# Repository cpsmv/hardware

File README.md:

# CPSMV EAGLE Library Specifications #

Please follow these guidelines for all PCBs for the Supermileage vehicle.

### EAGLE: 

##### Schematic:
   * Grid size: 100 mil (default)

##### PCB Layout:
   * Silkscreen text size:   40 mil 
   * Silkscreen text ratio:  15% 
   * Silkscreen text font:   Vector 

##### Gerbers:

When generating Gerbers, please use the following layers:
   * 1  - Top 
   * 16 - Bottom
   * 17 - Pads
   * 18 - Vias
   * 21 - tPlace
   * 22 - bPlace (if any silkscreen on bottom of board)
   * 25 - tNames
   * 27 - tValues
   * 29 - tStop
   * 39 - tKeepout
   * 44 - Drills
   * 45 - Holes

Notes:
   * Use layers 2-15 if the board is more than 2 layers 
   * Layer 51 tDocu & 52 bDocu are not to be used for silkscreen

### Advanced Circuits: 
   * General fab specs:    http://www.4pcb.com/pcb-design-specifications/ 
   * 2 layer board specs:  http://www.4pcb.com/33-each-pcbs/index.html 
   * 4 layer board specs:  http://www.4pcb.com/66-each-pcbs/index.html

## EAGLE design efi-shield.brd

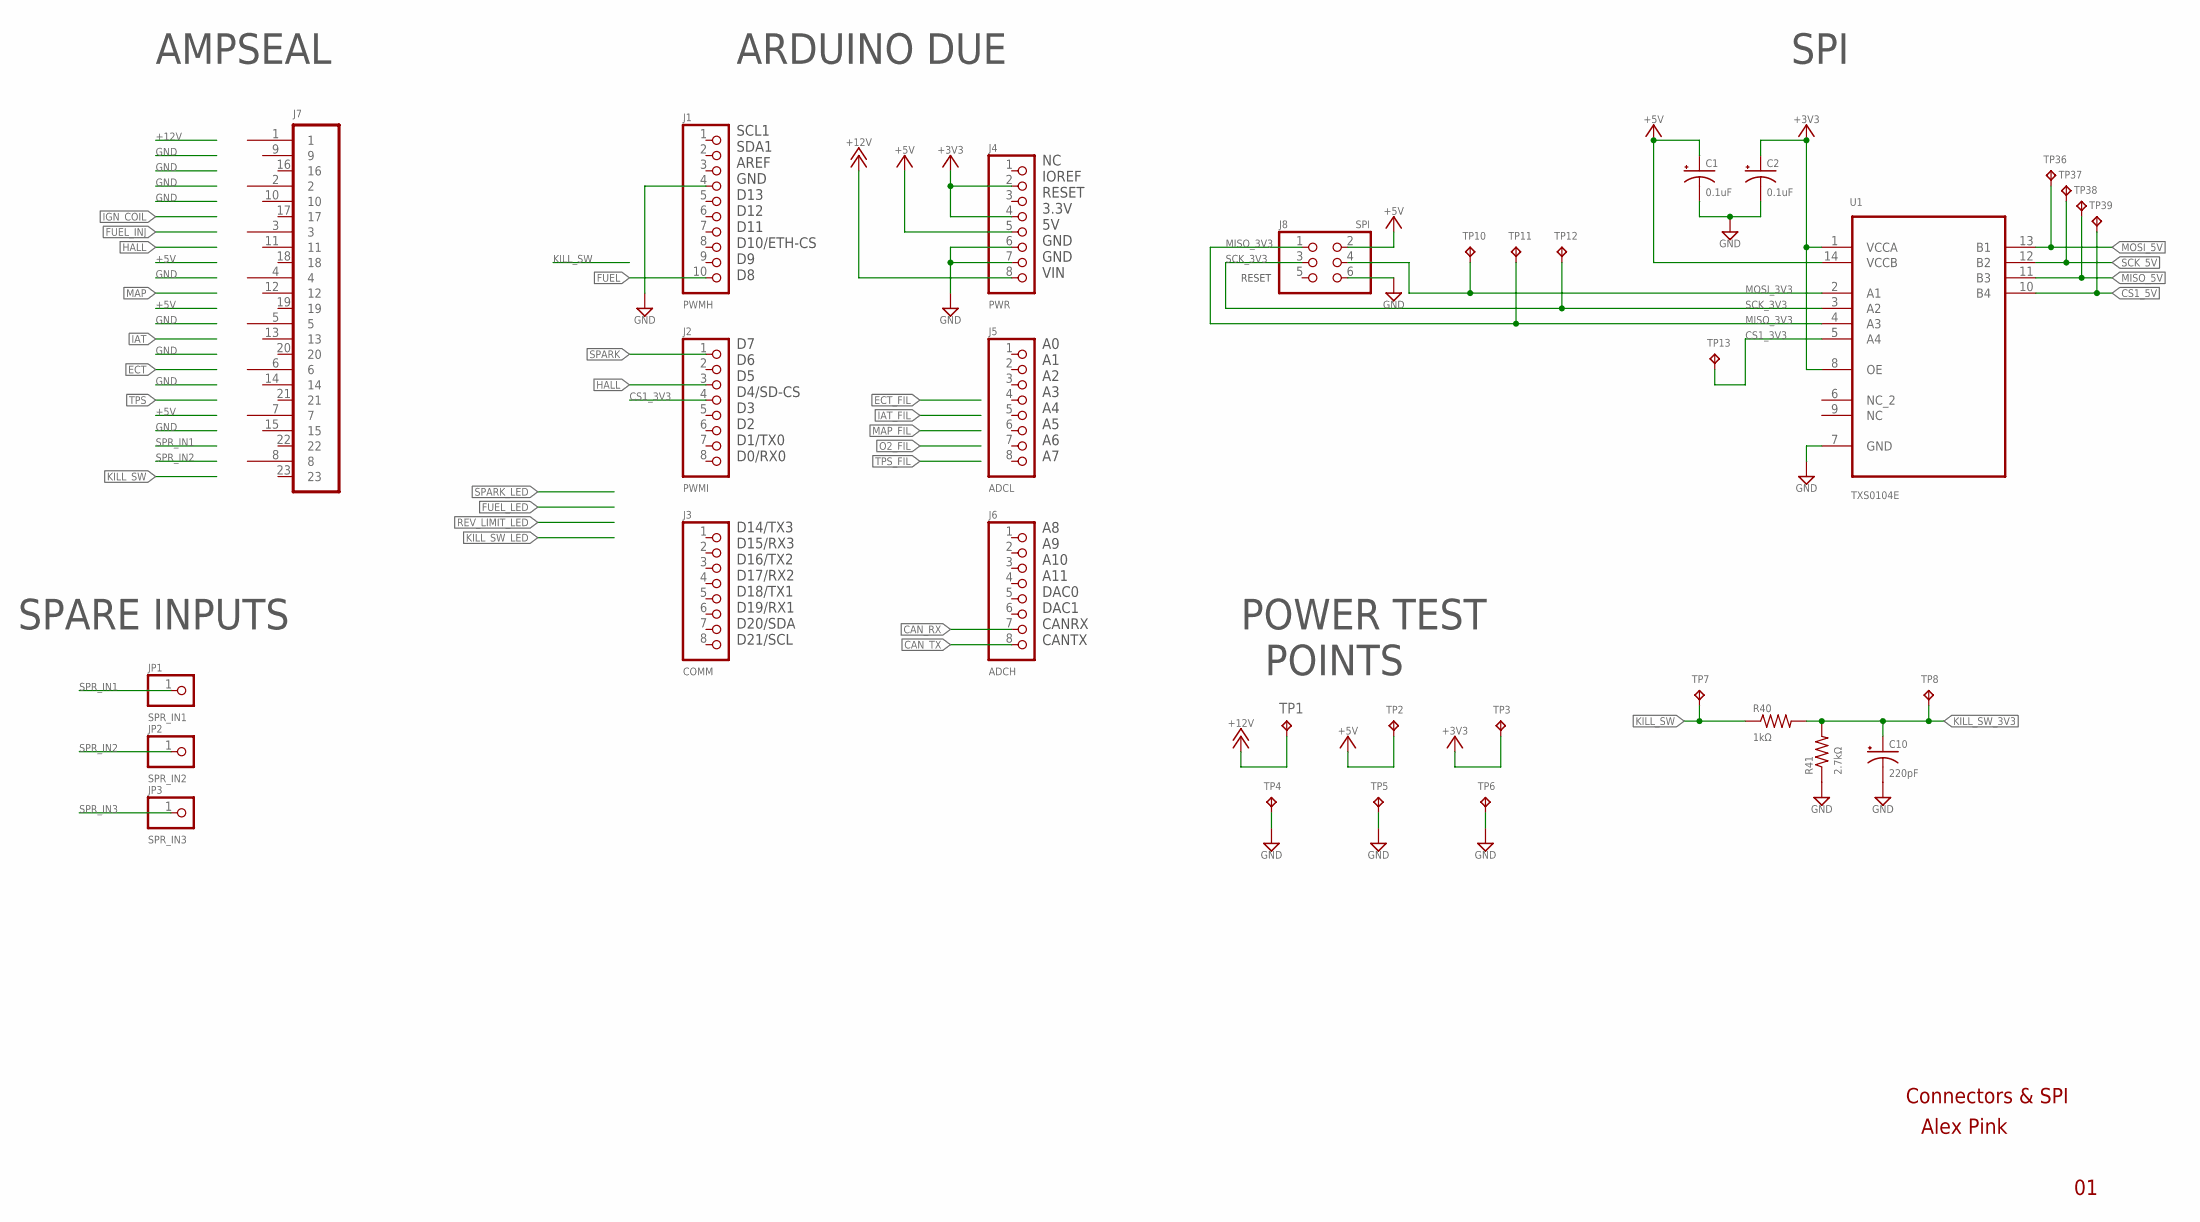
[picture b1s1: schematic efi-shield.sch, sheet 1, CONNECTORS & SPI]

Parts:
C1, C2: 0.1uF; C050-025X075
C10: 220pF; C050-025X075
J1: PWMH; 1X10
J2: PWMI; 1X08
J3: COMM; 1X08
J4: PWR; 1X08
J5: ADCL; 1X08
J6: ADCH; 1X08
J7: AMPSEAL-23POS-HEADER; AMPSEAL-HEADER-23POS-RA
J8: SPI; 2X03
JP1: SPR_IN1; 1X01
JP2: SPR_IN2; 1X01
JP3: SPR_IN3; 1X01
R40: 1kΩ; 0207/7
R41: 2.7kΩ; 0207/7
TP1: +12V; TP-P1-20
TP2: +5V; TP-P1-20
TP3: +3V3; TP-P1-20
TP4, TP5, TP6: GND; TP-P1-20
TP7: KILL_SW; TP-P1-20
TP8: KILL_SW_3V3; TP-P1-20
TP10: MOSI_3V3; TP-P1-20
TP11: MISO_3V3; TP-P1-20
TP12: SCK_3V3; TP-P1-20
TP13: CS1_3V3; TP-P1-20
TP36: MOSI_5V; TP-P1-20
TP37: SCK_5V; TP-P1-20
TP38: MISO_5V; TP-P1-20
TP39: CS1_5V; TP-P1-20
U1: TXS0104E; SOIC127P600X175-14N

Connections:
+3V3: C2.1, J4.2, J4.4, TP3.TP, U1.1 (VCCA), U1.8 (OE)
+5V: C1.1, J4.5, J8.2, TP2.TP, U1.14 (VCCB); also elsewhere on the board
+12V: J4.8, TP1.TP; also elsewhere on the board
CAN_RX: J6.7; also elsewhere on the board
CAN_TX: J6.8; also elsewhere on the board
CS1_3V3: J2.4, TP13.TP, U1.5 (A4)
CS1_5V: TP39.TP, U1.10 (B4)
FUEL: J1.10; also elsewhere on the board
GND: C1.2, C2.2, C10.2, J1.4, J4.6, J4.7, J8.6, R41.1, TP4.TP, TP5.TP, TP6.TP, U1.7 (GND); also elsewhere on the board
HALL: J2.3; also elsewhere on the board
KILL_SW: R40.1, TP7.TP
KILL_SW_3V3: C10.1, R40.2, R41.2, TP8.TP
MISO_3V3: J8.1, TP11.TP, U1.4 (A3)
MISO_5V: TP38.TP, U1.11 (B3)
MOSI_3V3: J8.4, TP10.TP, U1.2 (A1)
MOSI_5V: TP36.TP, U1.13 (B1)
SCK_3V3: J8.3, TP12.TP, U1.3 (A2)
SCK_5V: TP37.TP, U1.12 (B2)
SPARK: J2.1; also elsewhere on the board
SPR_IN1: JP1.1
SPR_IN2: JP2.1
SPR_IN3: JP3.1

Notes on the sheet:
SCL1 SDA1 AREF GND D13 D12 D11 D10/ETH-CS D9 D8
D7 D6 D5 D4/SD-CS D3 D2 D1/TX0 D0/RX0
D14/TX3 D15/RX3 D16/TX2 D17/RX2 D18/TX1 D19/RX1 D20/SDA D21/SCL
NC IOREF RESET 3.3V 5V GND GND VIN
A0 A1 A2 A3 A4 A5 A6 A7
A8 A9 A10 A11 DAC0 DAC1 CANRX CANTX
ARDUINO DUE
AMPSEAL
RESET
SPI
SPARE INPUTS
Alex Pink
Connectors & SPI
POWER TEST POINTS

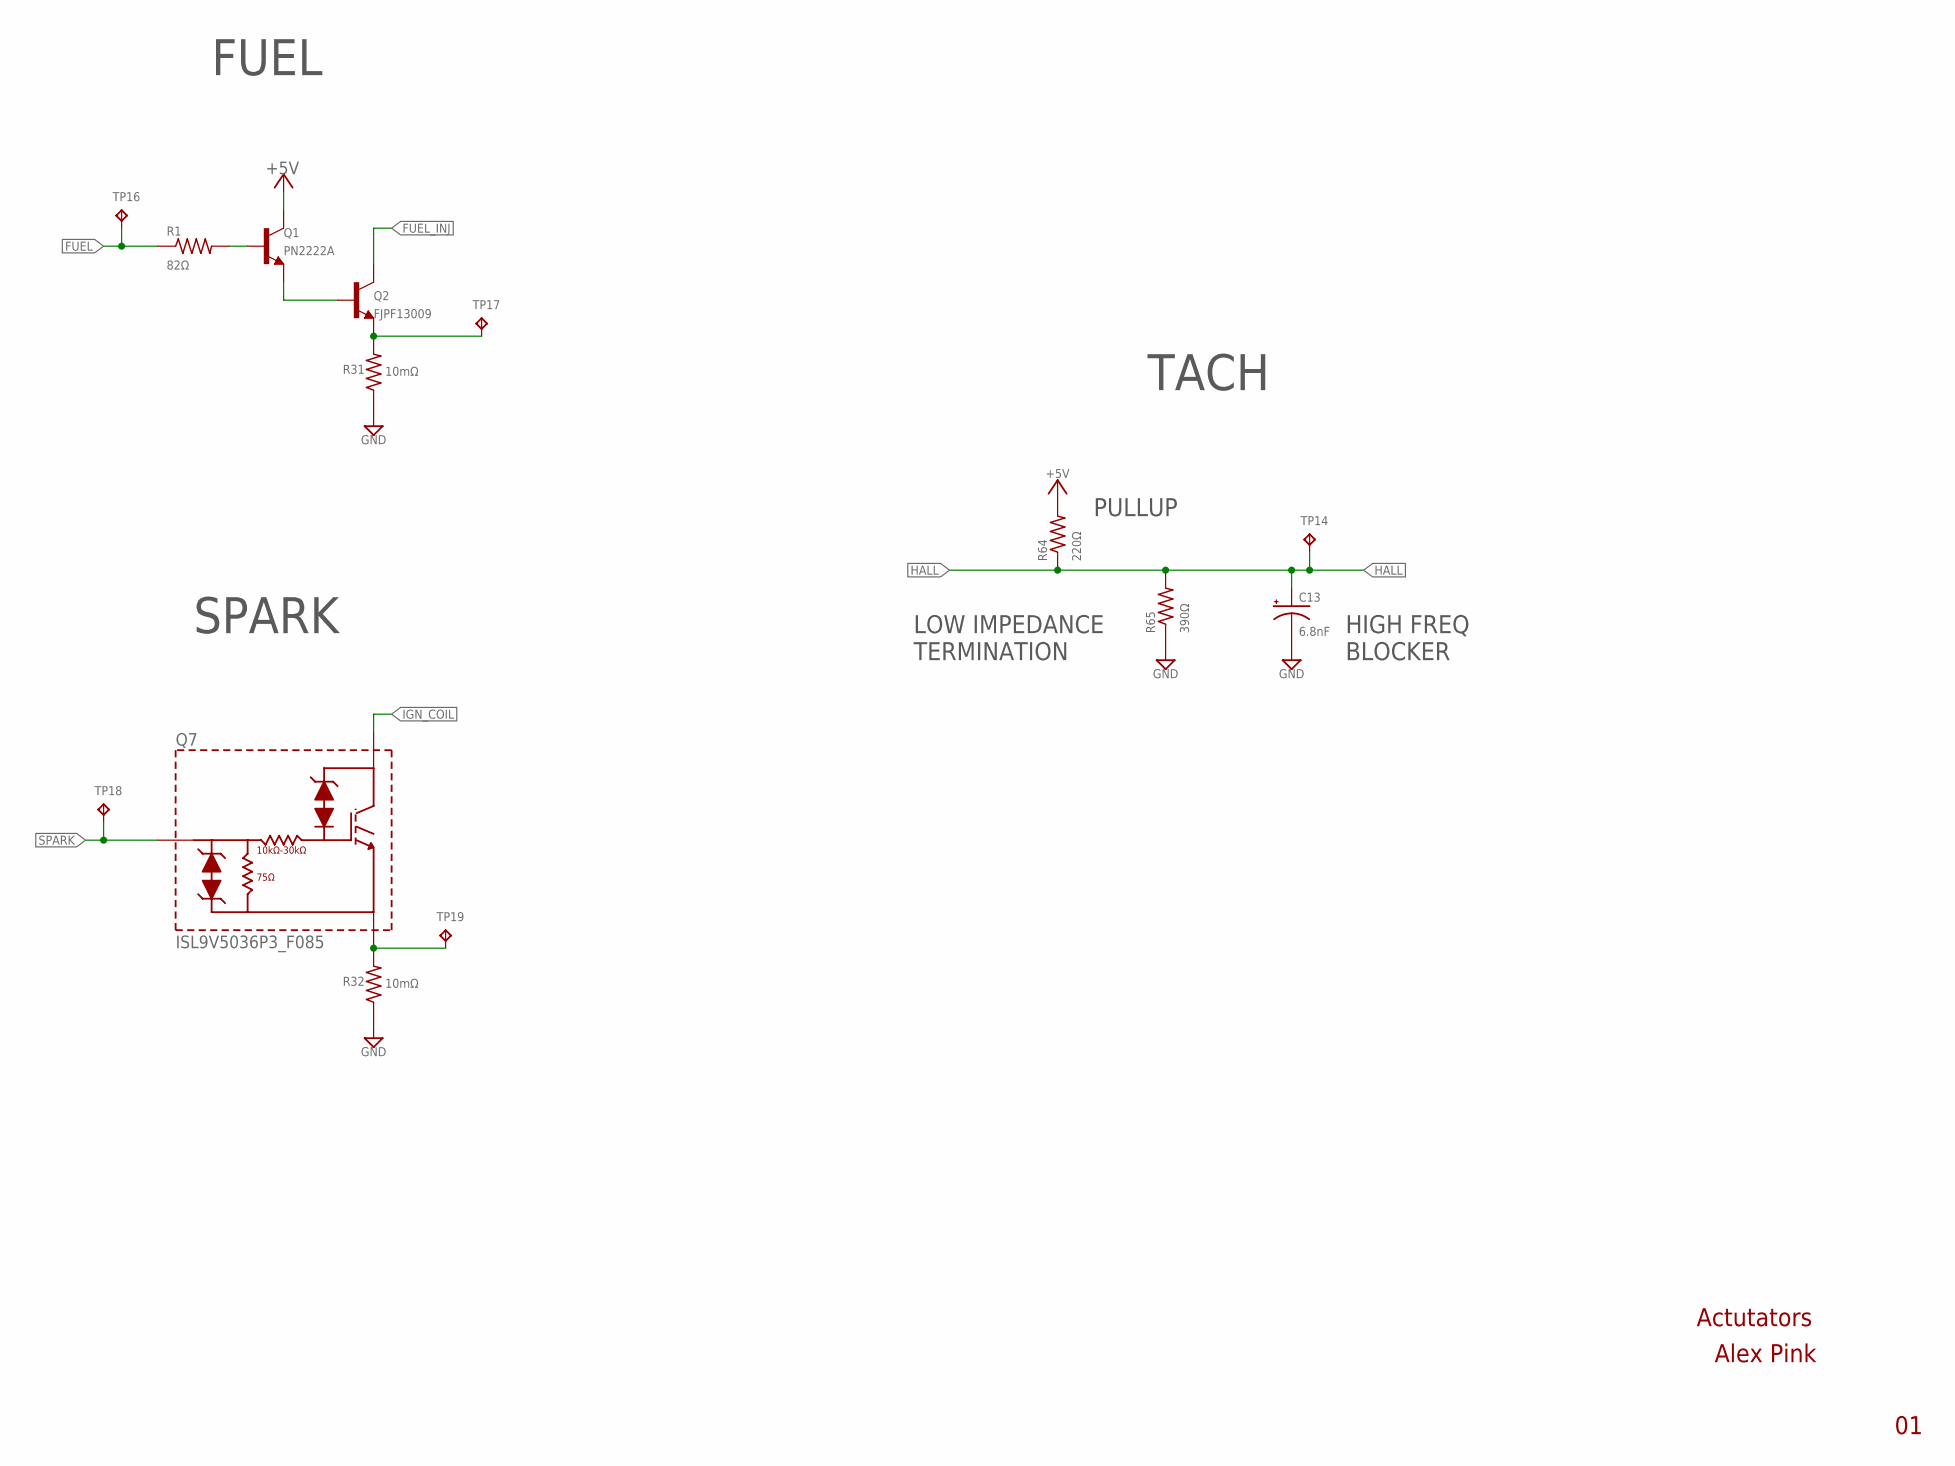
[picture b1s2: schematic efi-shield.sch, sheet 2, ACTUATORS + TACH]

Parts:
C13: 6.8nF; C050-025X075
Q1: PN2222A; TO92-EBC
Q2: FJPF13009; TO220
Q7: ISL9V5036P3_F085; TO220AB
R1: 82Ω; 0207/7
R31, R32: 10mΩ; 0514/15
R64: 220Ω; 0207/7
R65: 390Ω; 0207/7
TP14: HALL; TP-P1-20
TP16: FUEL; TP-P1-20
TP17: FUEL_E; TP-P1-20
TP18: SPARK; TP-P1-20
TP19: SPARK_E; TP-P1-20

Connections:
+5V: Q1.C, R64.2; also elsewhere on the board
FUEL: R1.1, TP16.TP; also elsewhere on the board
FUEL_INJ: Q2.2 (C)
GND: C13.2, R31.1, R32.1, R65.1; also elsewhere on the board
HALL: C13.1, R64.1, R65.2, TP14.TP; also elsewhere on the board
IGN_COIL: Q7.2 (C)
unnamed: Q1.B, R1.2
unnamed: Q1.E, Q2.1 (B)
unnamed: Q7.3 (E), R32.2, TP19.TP
unnamed: Q2.3 (E), R31.2, TP17.TP
SPARK: Q7.1 (G), TP18.TP; also elsewhere on the board

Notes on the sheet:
FUEL
Alex Pink
Actutators
SPARK
TACH
LOW IMPEDANCE TERMINATION
PULLUP
HIGH FREQ BLOCKER

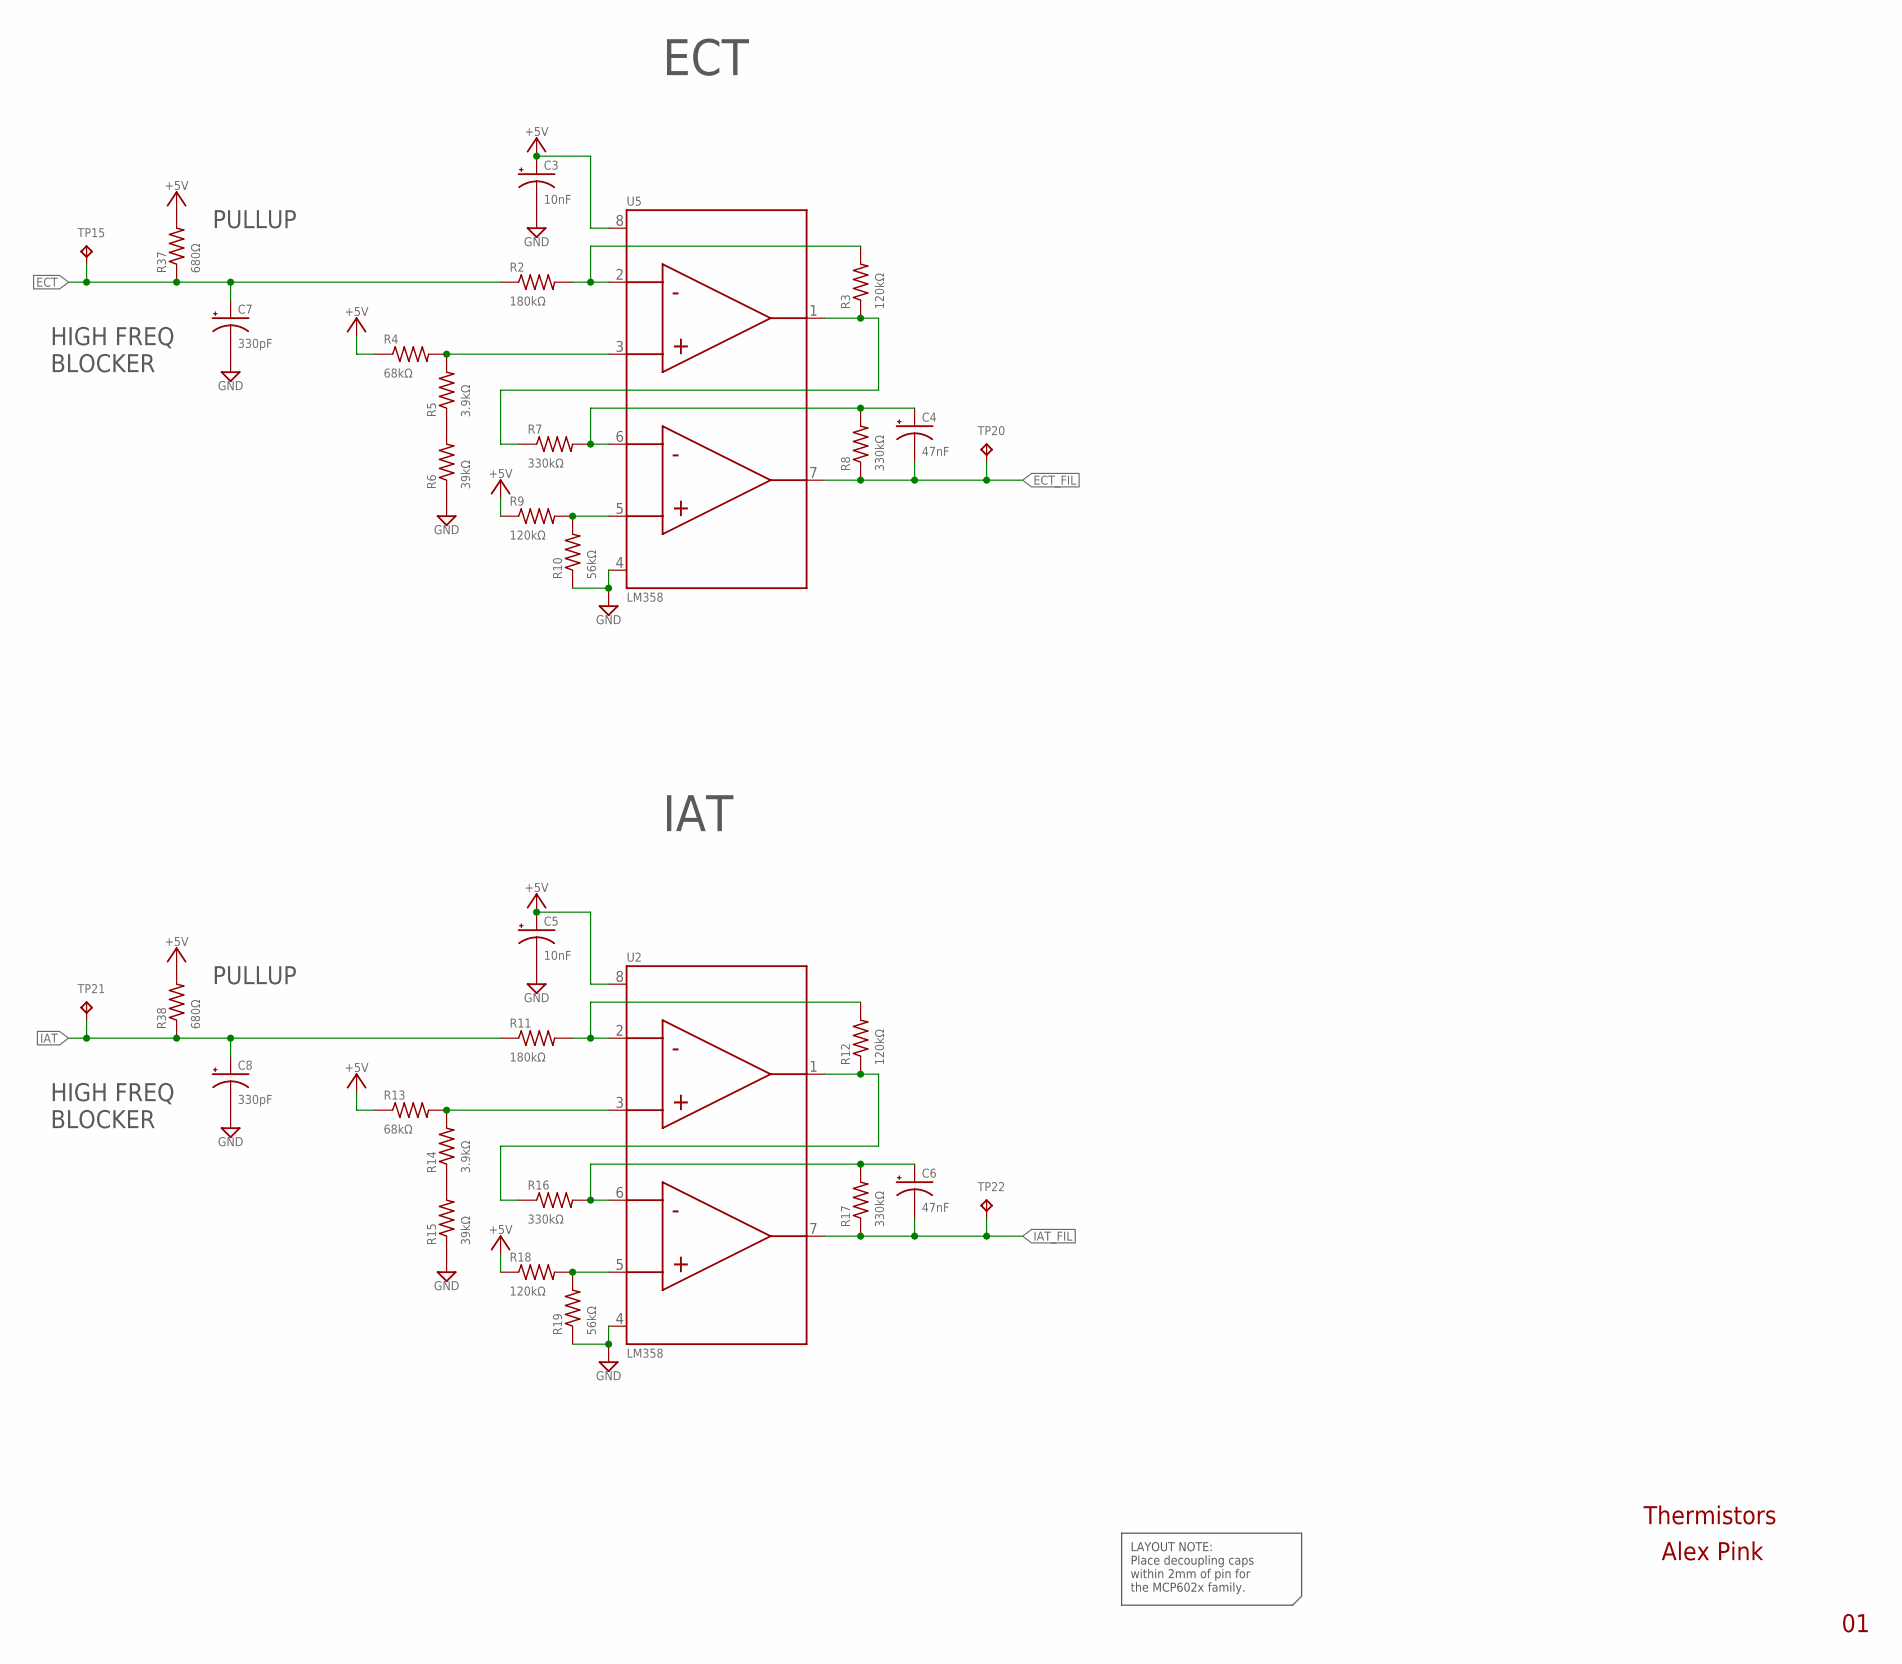
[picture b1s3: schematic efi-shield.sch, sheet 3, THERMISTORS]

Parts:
C3, C5: 10nF; C050-025X075
C4, C6: 47nF; C050-025X075
C7, C8: 330pF; C050-025X075
R2, R11: 180kΩ; 0207/7
R3, R9, R12, R18: 120kΩ; 0207/7
R4, R13: 68kΩ; 0207/7
R5, R14: 3.9kΩ; 0207/7
R6, R15: 39kΩ; 0207/7
R7, R8, R16, R17: 330kΩ; 0207/7
R10, R19: 56kΩ; 0207/7
R37, R38: 680Ω; 0207/7
TP15: ECT; TP-P1-20
TP20: ECT_FIL; TP-P1-20
TP21: IAT; TP-P1-20
TP22: IAT_FIL; TP-P1-20
U2, U5: LM358; SOP08

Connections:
+5V: C3.1, C5.1, R4.1, R9.1, R13.1, R18.1, R37.2, R38.2, U2.8 (VDD), U5.8 (VDD); also elsewhere on the board
ECT: C7.1, R2.1, R37.1, TP15.TP
ECT_FIL: C4.2, R8.1, TP20.TP, U5.7 (VOUTB)
GND: C3.2, C5.2, C7.2, C8.2, R6.1, R10.1, R15.1, R19.1, U2.4 (VSS), U5.4 (VSS); also elsewhere on the board
IAT: C8.1, R11.1, R38.1, TP21.TP
IAT_FIL: C6.2, R17.1, TP22.TP, U2.7 (VOUTB)
unnamed: R4.2, R5.2, U5.3 (VINA+)
unnamed: R9.2, R10.2, U5.5 (VINB+)
unnamed: R2.2, R3.2, U5.2 (VINA-)
unnamed: R3.1, R7.1, U5.1 (VOUTA)
unnamed: C4.1, R7.2, R8.2, U5.6 (VINB-)
unnamed: R13.2, R14.2, U2.3 (VINA+)
unnamed: R5.1, R6.2
unnamed: R18.2, R19.2, U2.5 (VINB+)
unnamed: R11.2, R12.2, U2.2 (VINA-)
unnamed: R12.1, R16.1, U2.1 (VOUTA)
unnamed: C6.1, R16.2, R17.2, U2.6 (VINB-)
unnamed: R14.1, R15.2

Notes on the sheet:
LAYOUT NOTE: Place decoupling caps within 2mm of pin for the MCP602x family.
Alex Pink
Thermistors
ECT
IAT
PULLUP
HIGH FREQ BLOCKER

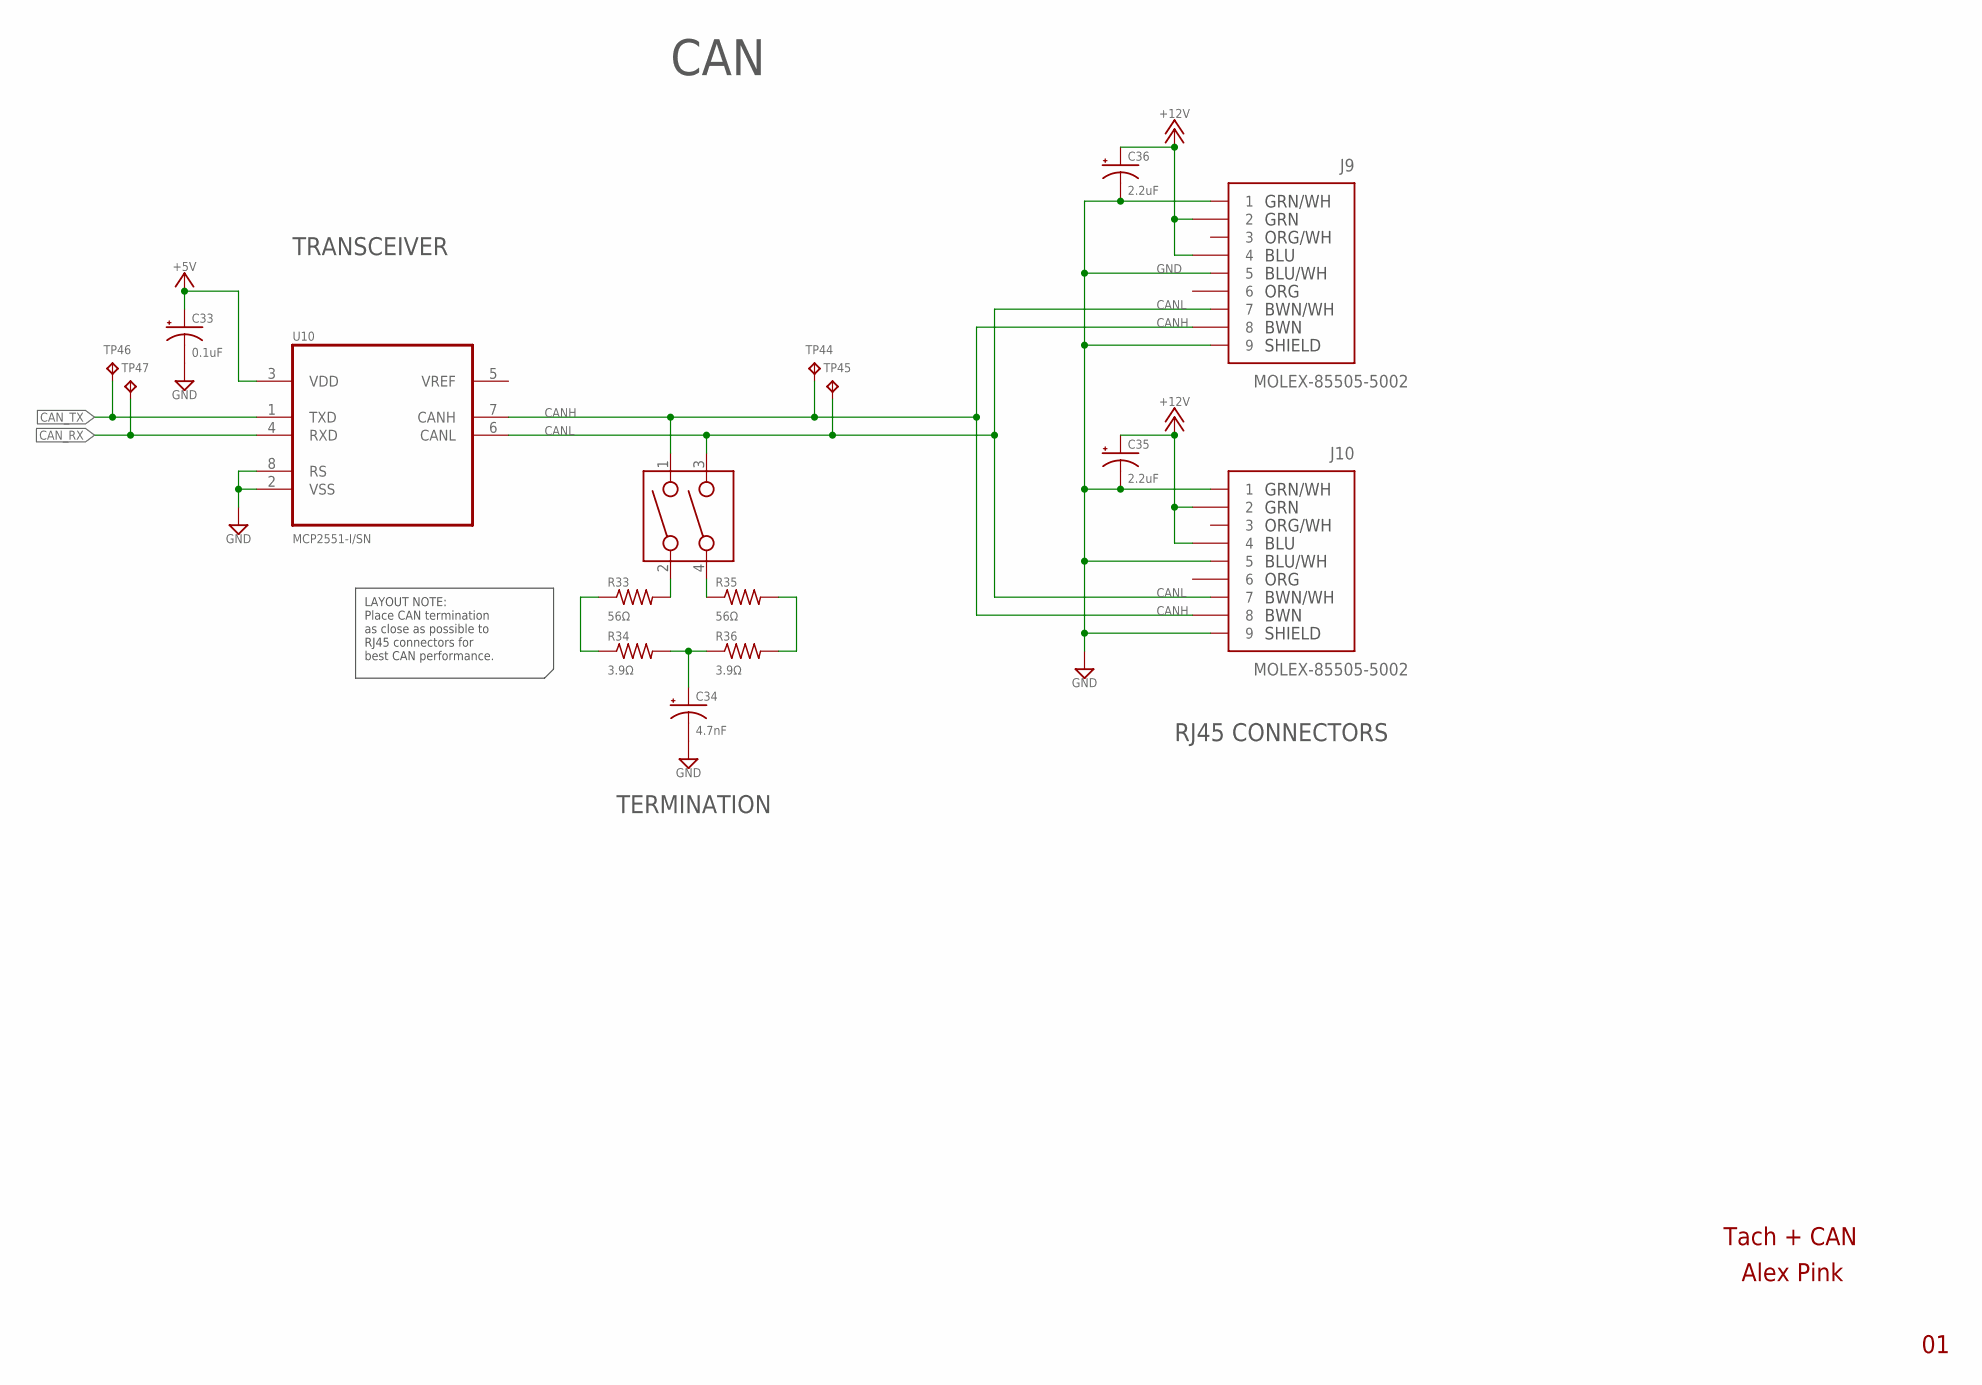
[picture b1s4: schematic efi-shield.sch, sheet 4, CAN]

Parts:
C33: 0.1uF; C050-025X075
C34: 4.7nF; C050-025X075
C35, C36: 2.2uF; C050-025X075
J9, J10: MOLEX-85505-5002; 85505-5002
R33, R35: 56Ω; 0207/7
R34, R36: 3.9Ω; 0207/7
SW1: CTS-204-211ST; 204-211ST
TP44: CANH; TP-P1-20
TP45: CANL; TP-P1-20
TP46: CAN_TX; TP-P1-20
TP47: CAN_RX; TP-P1-20
U10: MCP2551-I/SN; SOIC127P600X175-8N

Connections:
+5V: C33.1, U10.3 (VDD); also elsewhere on the board
+12V: C35.1, C36.1, J9.2, J9.4, J10.2, J10.4; also elsewhere on the board
CANH: J9.8, J10.8, SW1.1, TP44.TP, U10.7 (CANH)
CANL: J9.7, J10.7, SW1.3, TP45.TP, U10.6 (CANL)
CAN_RX: TP47.TP, U10.4 (RXD); also elsewhere on the board
CAN_TX: TP46.TP, U10.1 (TXD); also elsewhere on the board
GND: C33.2, C34.2, C35.2, C36.2, J9.1, J9.5, J9.9, J9.10 (9), J10.1, J10.5, J10.9, J10.10 (9), U10.2 (VSS), U10.8 (RS); also elsewhere on the board
unnamed: R33.2, SW1.2
unnamed: R35.1, SW1.4
unnamed: R33.1, R34.1
unnamed: R35.2, R36.2
unnamed: C34.1, R34.2, R36.1

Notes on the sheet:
Alex Pink
Tach + CAN
LAYOUT NOTE: Place CAN termination as close as possible to RJ45 connectors for best CAN performance.
TRANSCEIVER
TERMINATION
RJ45 CONNECTORS
CAN

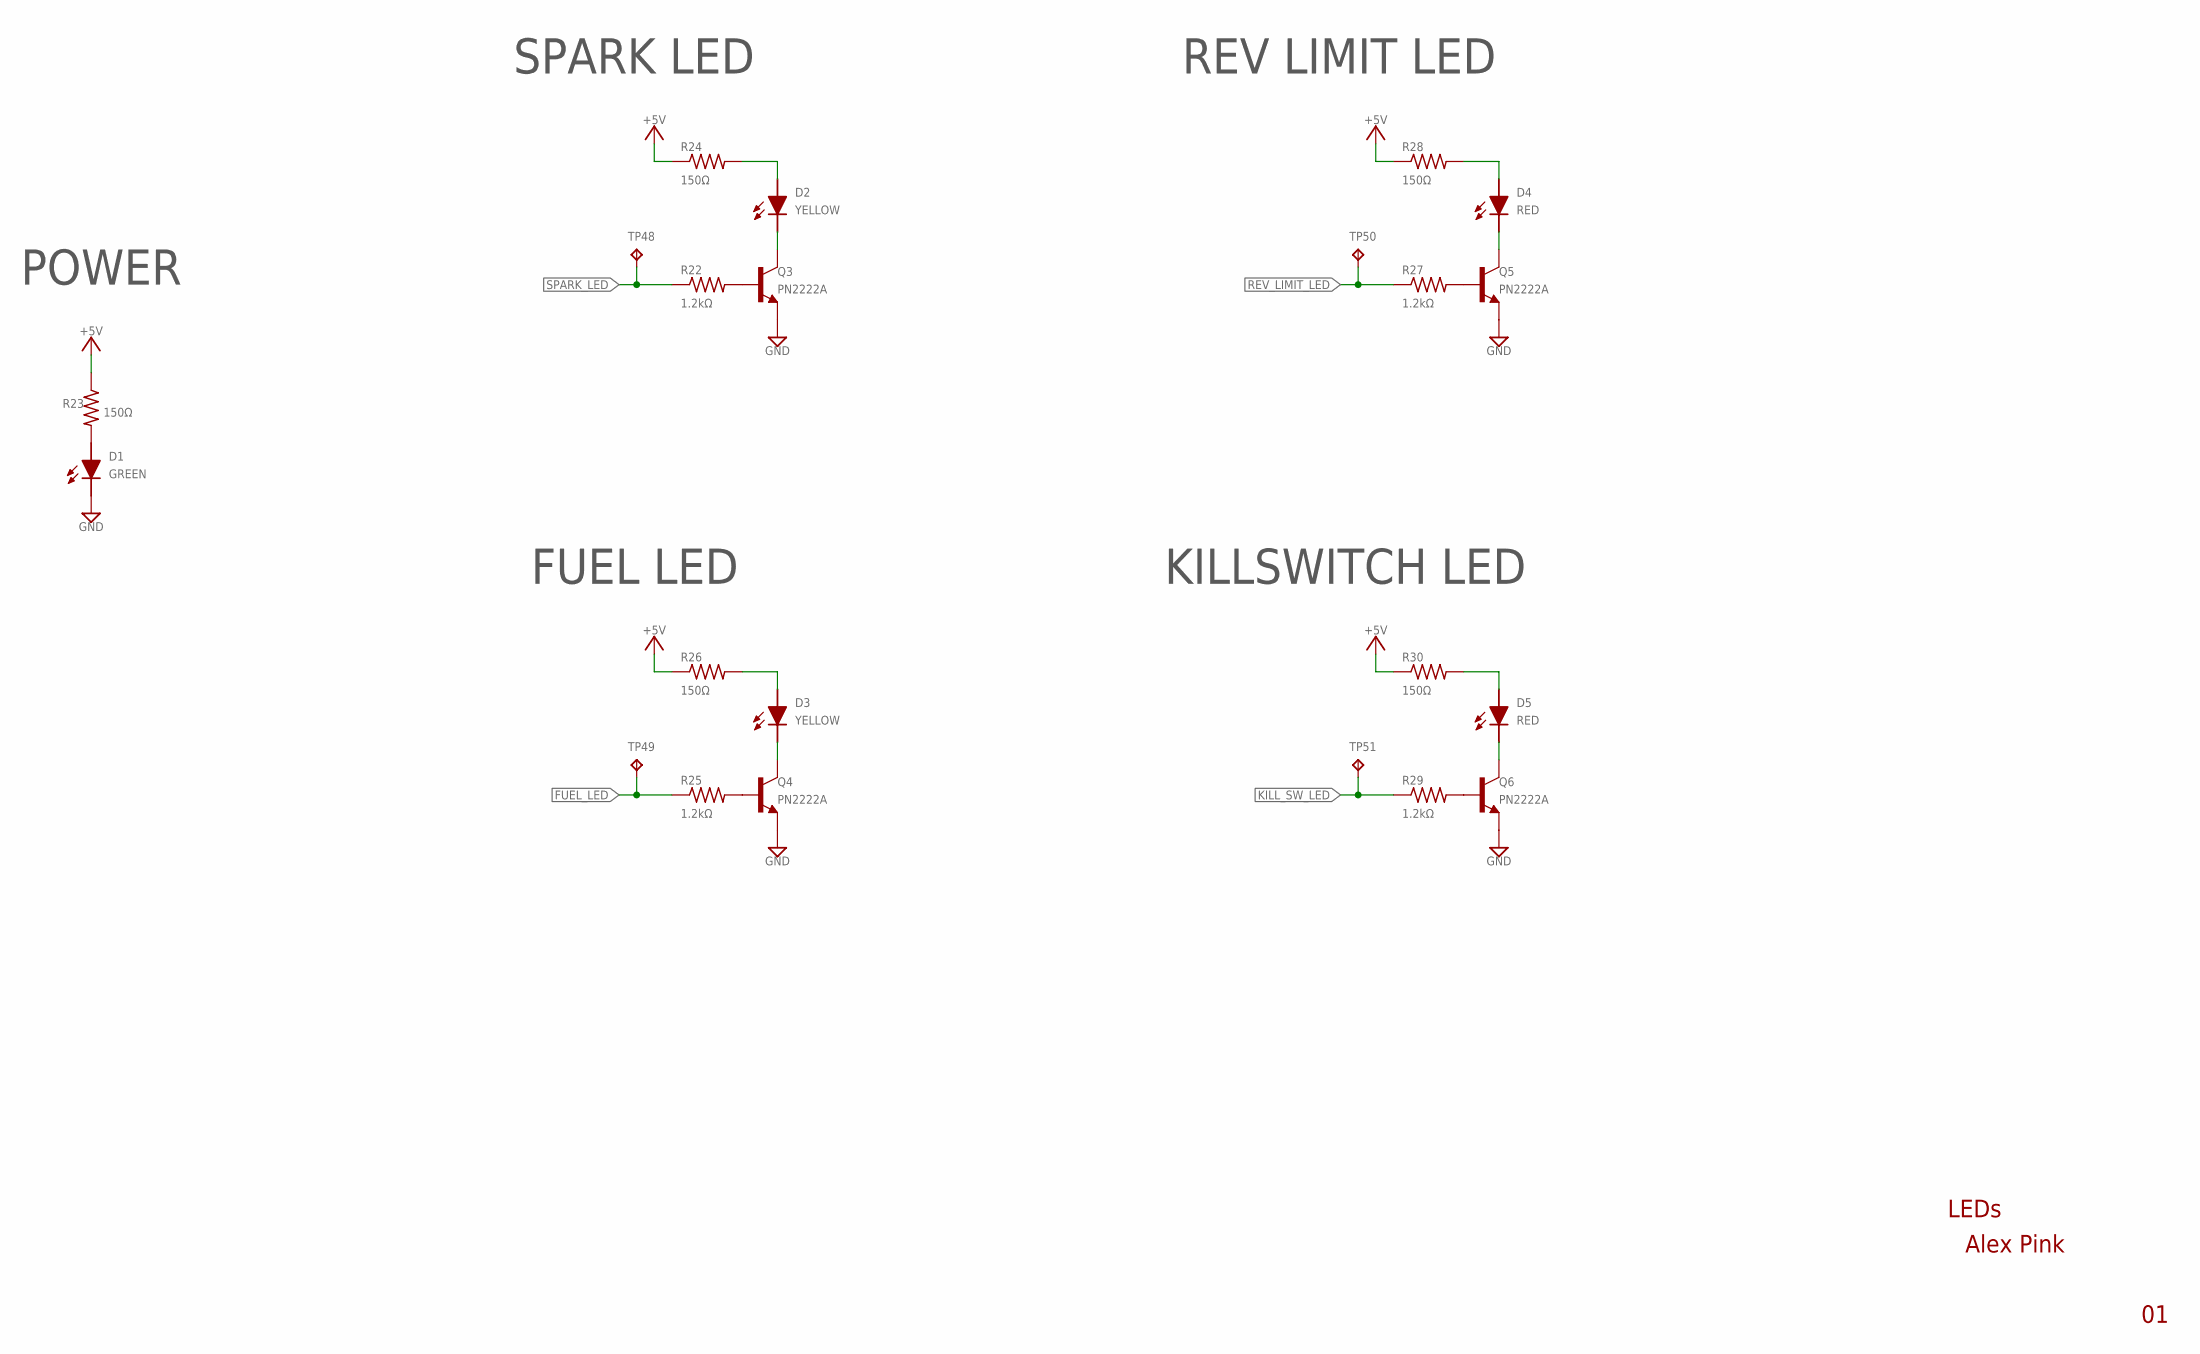
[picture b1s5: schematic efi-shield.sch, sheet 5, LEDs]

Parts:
D1: GREEN; LED,THRU-HOLE,R/A
D2, D3: YELLOW; LED,THRU-HOLE,R/A
D4, D5: RED; LED,THRU-HOLE,R/A
Q3, Q4, Q5, Q6: PN2222A; TO92-EBC
R22, R25, R27, R29: 1.2kΩ; 0207/7
R23, R24, R26, R28, R30: 150Ω; 0207/7
TP48: SPARK_LED; TP-P1-20
TP49: FUEL_LED; TP-P1-20
TP50: REV_LIMIT_LED; TP-P1-20
TP51: KILL_SW_LED; TP-P1-20

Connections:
+5V: R23.1, R24.1, R26.1, R28.1, R30.1; also elsewhere on the board
FUEL_LED: R25.1, TP49.TP
GND: D1.CATHODE, Q3.E, Q4.E, Q5.E, Q6.E; also elsewhere on the board
KILL_SW_LED: R29.1, TP51.TP
unnamed: D2.CATHODE, Q3.C
unnamed: D2.ANODE, R24.2
unnamed: D1.ANODE, R23.2
unnamed: Q3.B, R22.2
unnamed: D3.CATHODE, Q4.C
unnamed: D3.ANODE, R26.2
unnamed: Q4.B, R25.2
unnamed: D4.CATHODE, Q5.C
unnamed: D4.ANODE, R28.2
unnamed: Q5.B, R27.2
unnamed: D5.CATHODE, Q6.C
unnamed: D5.ANODE, R30.2
unnamed: Q6.B, R29.2
REV_LIMIT_LED: R27.1, TP50.TP
SPARK_LED: R22.1, TP48.TP

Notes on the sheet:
Alex Pink
LEDs
POWER
SPARK LED
FUEL LED
REV LIMIT LED
KILLSWITCH LED

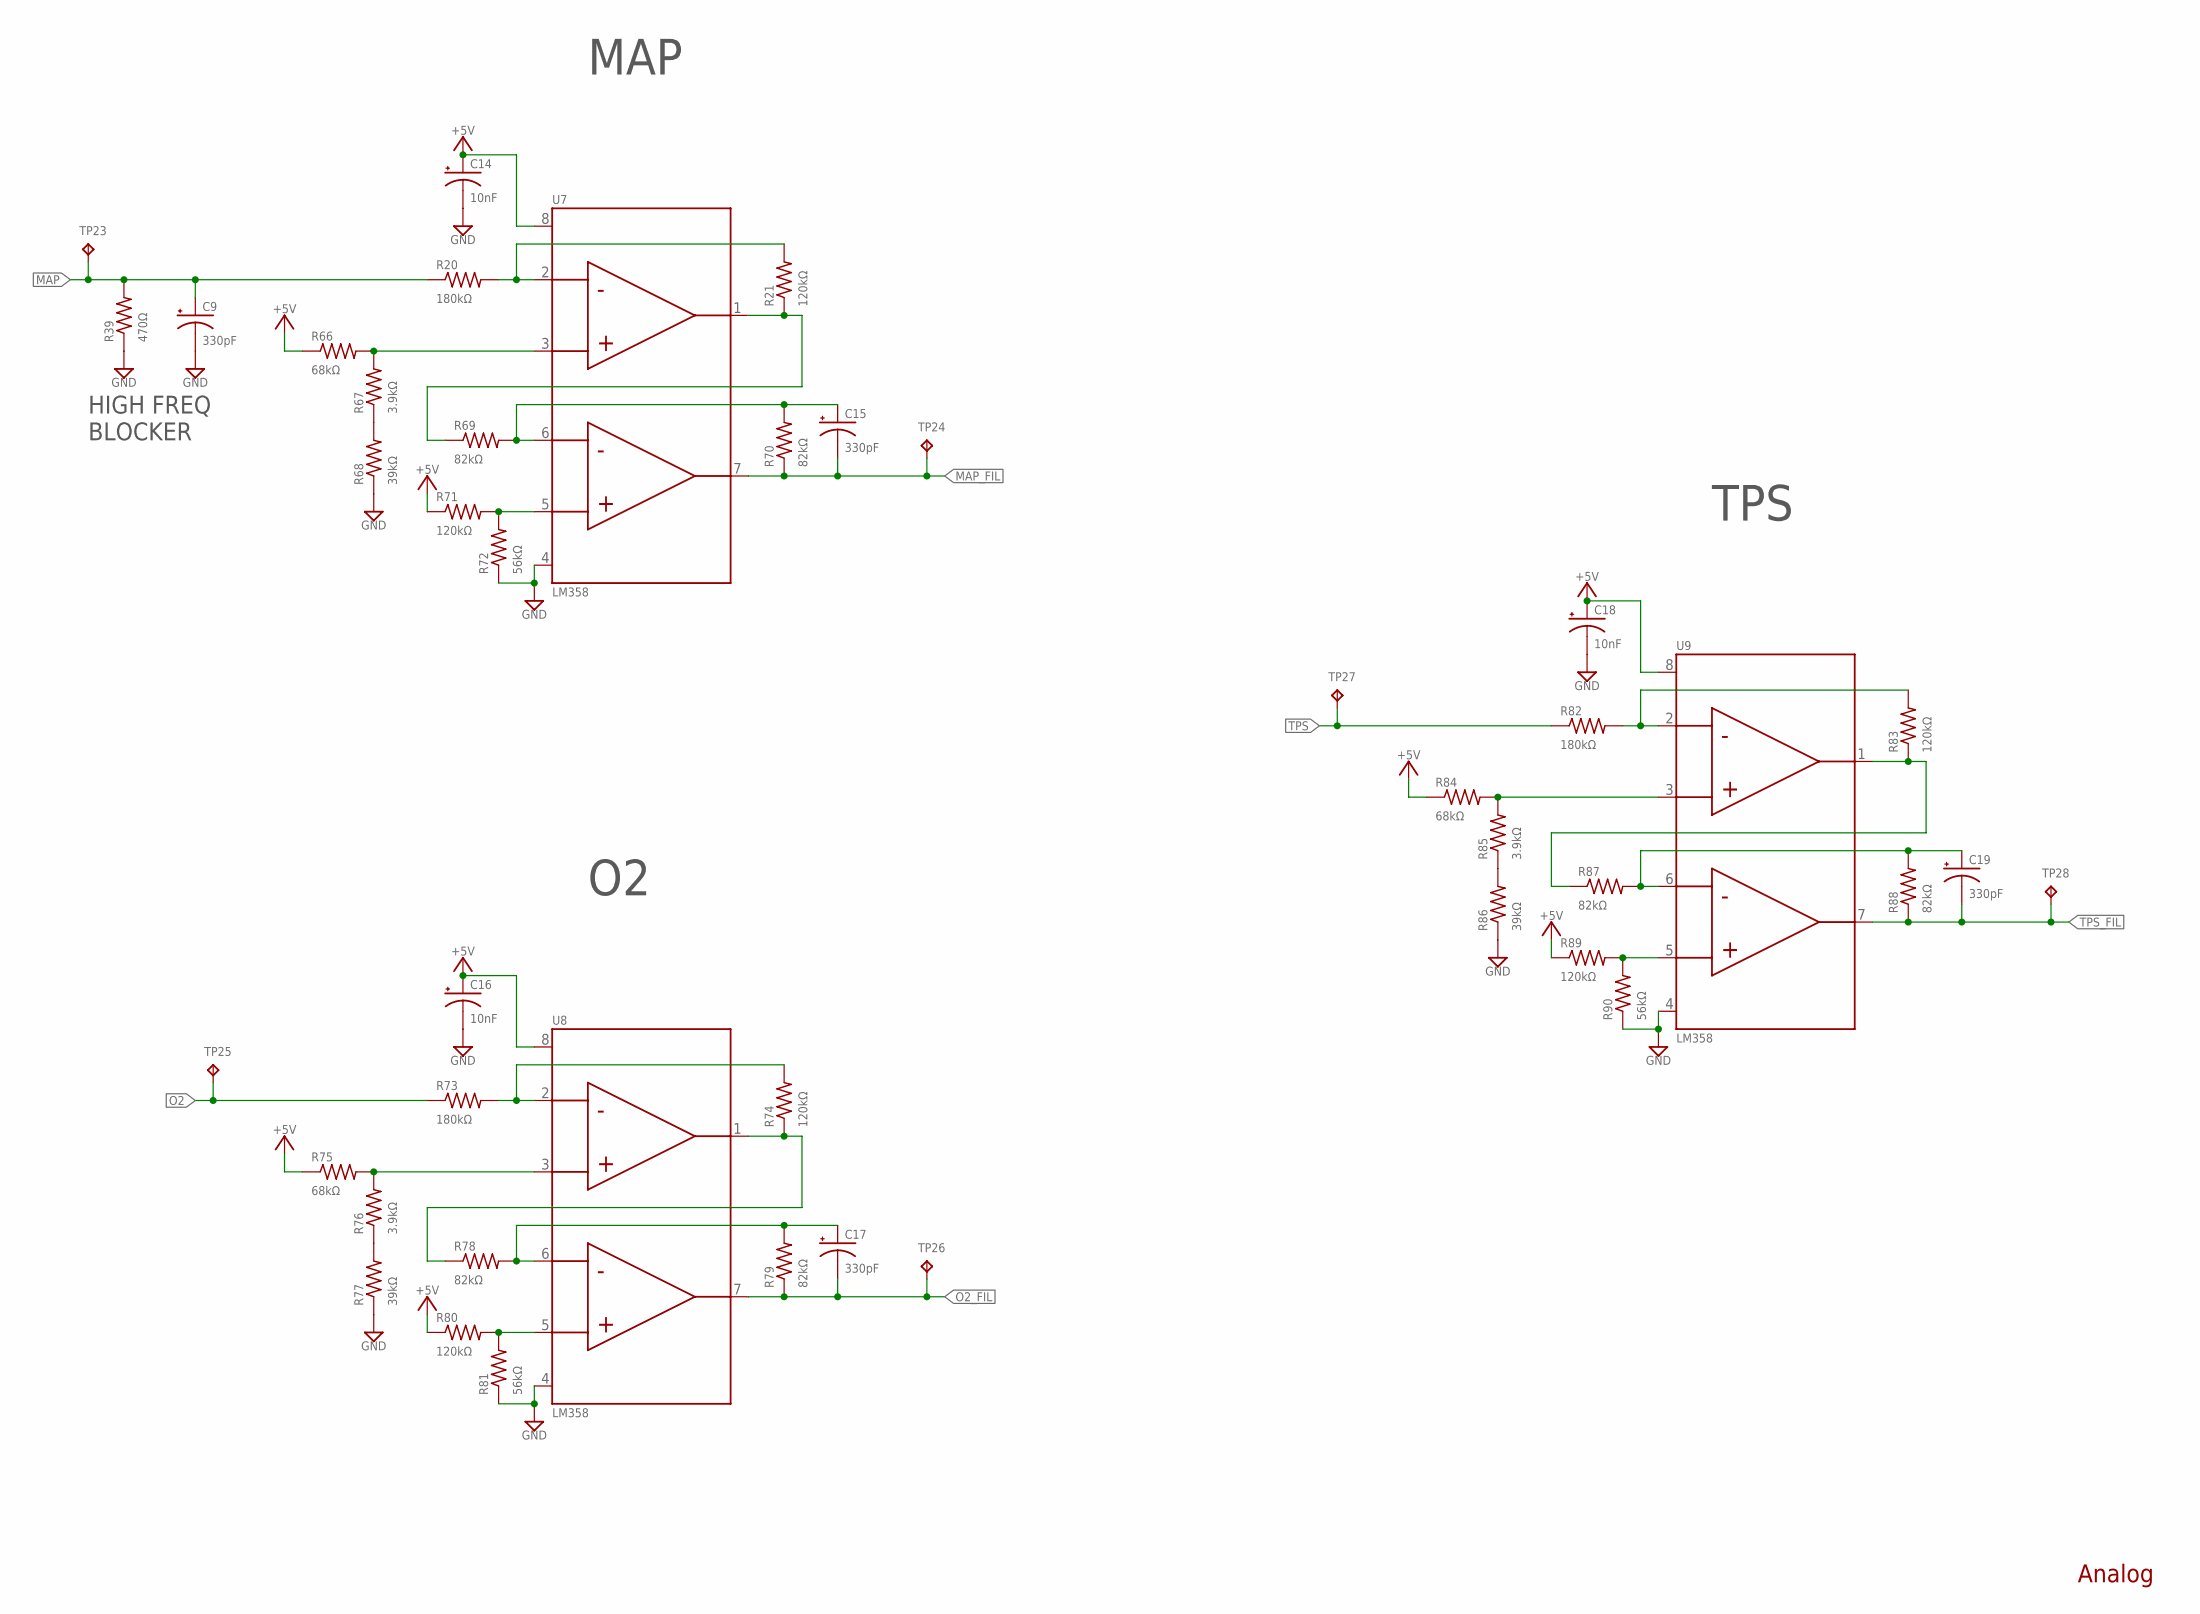
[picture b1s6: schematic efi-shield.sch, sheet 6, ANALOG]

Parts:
C9, C15, C17, C19: 330pF; C050-025X075
C14, C16, C18: 10nF; C050-025X075
R20, R73, R82: 180kΩ; 0207/7
R21, R71, R74, R80, R83, R89: 120kΩ; 0207/7
R39: 470Ω; 0207/7
R66, R75, R84: 68kΩ; 0207/7
R67, R76, R85: 3.9kΩ; 0207/7
R68, R77, R86: 39kΩ; 0207/7
R69, R70, R78, R79, R87, R88: 82kΩ; 0207/7
R72, R81, R90: 56kΩ; 0207/7
TP23: MAP; TP-P1-20
TP24: MAP_FIL; TP-P1-20
TP25: O2; TP-P1-20
TP26: O2_FIL; TP-P1-20
TP27: TPS; TP-P1-20
TP28: TPS_FIL; TP-P1-20
U7, U8, U9: LM358; SOP08

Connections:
+5V: C14.1, C16.1, C18.1, R66.1, R71.1, R75.1, R80.1, R84.1, R89.1, U7.8 (VDD), U8.8 (VDD), U9.8 (VDD); also elsewhere on the board
GND: C9.2, C14.2, C16.2, C18.2, R39.1, R68.1, R72.1, R77.1, R81.1, R86.1, R90.1, U7.4 (VSS), U8.4 (VSS), U9.4 (VSS); also elsewhere on the board
MAP: C9.1, R20.1, R39.2, TP23.TP
MAP_FIL: C15.2, R70.1, TP24.TP, U7.7 (VOUTB)
unnamed: R66.2, R67.2, U7.3 (VINA+)
unnamed: R71.2, R72.2, U7.5 (VINB+)
unnamed: R20.2, R21.2, U7.2 (VINA-)
unnamed: R21.1, R69.1, U7.1 (VOUTA)
unnamed: C15.1, R69.2, R70.2, U7.6 (VINB-)
unnamed: R67.1, R68.2
unnamed: R75.2, R76.2, U8.3 (VINA+)
unnamed: R80.2, R81.2, U8.5 (VINB+)
unnamed: R73.2, R74.2, U8.2 (VINA-)
unnamed: R74.1, R78.1, U8.1 (VOUTA)
unnamed: C17.1, R78.2, R79.2, U8.6 (VINB-)
unnamed: R76.1, R77.2
unnamed: R84.2, R85.2, U9.3 (VINA+)
unnamed: R89.2, R90.2, U9.5 (VINB+)
unnamed: R82.2, R83.2, U9.2 (VINA-)
unnamed: R83.1, R87.1, U9.1 (VOUTA)
unnamed: C19.1, R87.2, R88.2, U9.6 (VINB-)
unnamed: R85.1, R86.2
O2: R73.1, TP25.TP
O2_FIL: C17.2, R79.1, TP26.TP, U8.7 (VOUTB)
TPS: R82.1, TP27.TP
TPS_FIL: C19.2, R88.1, TP28.TP, U9.7 (VOUTB)

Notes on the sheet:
MAP
TPS
Analog
HIGH FREQ BLOCKER
